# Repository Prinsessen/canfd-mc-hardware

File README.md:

# CANFD-MC — a minimal CAN board for a motorcycle

A 55 × 32 mm, 4-layer board that replaces the LilyGO T-2CANFD in the
[indian-thunderstroke-canbus](https://github.com/Prinsessen/indian-thunderstroke-canbus)
project: ESP32-S3-WROOM-1U + MCP2518FD + TCAN332G, fed from the bike's
permanent 12 V through an LM5164 buck. Same pin map as the LilyGO board, so the
firmware runs unchanged (`sniffer-t2can` environment).

What it drops from the LilyGO board, on purpose: the isolated transceiver (one
machine, one ground — the isolation was bridged the moment it was wired in, and
its DC-DC was three quarters of the sleep current), the USB connector, the screw
terminals, the second CAN channel, and the 120 Ω termination (the bike's bus is
already terminated; a third resistor is a stub). What it adds: a 6–40 V input
that survives load dump, four solder pads with strain-relief holes instead of
connectors, and a ~10 µA regulator so the board can live on the battery.

## Layout

```
canfd-mc.kicad_pro / .kicad_sch / .kicad_pcb   KiCad 10 project — placed, routed, DRC clean
canfd_local.pretty/                            three project footprints (solder pads with relief
                                               holes, Murata DLW43SH with Murata's pin numbering)
production/                                    what JLCPCB was sent: Gerber zip, BOM, CPL
docs/design-document.html                      the full design document: BOM, net list, the
                                               LM5164 calculation, layout rules, checklist
docs/BUILD-NOTES.md                            build, ordering and bring-up notes
docs/WIRING-PARTS.md                           antenna and service-connector cable to order
```

## Connections

Four wires from the service connector, soldered to plated pads along the bottom
edge — **CANL · CANH · GND · VBAT**. Each pad has an unplated 1.2 mm hole 3 mm
inboard: thread the wire up through the hole and down into the pad, so the
board takes the strain instead of the solder joint. No shield pad: the bus
shield is grounded at the ECM.

Flash header on the back (through-hole from rev 1.1, flat pads on rev 1.0), 2.54 mm pitch —
**GND · EN · TX · RX · IO0 · USB_D+ · USB_D−**.
First flash goes over the ESP32-S3's native USB (a cut USB cable on D+/D−/GND;
the board is powered from 12 V, not from USB). After that, OTA.

## Power input

| | |
|---|---|
| Input | 6–40 V (LM5164 is rated to 100 V; the TVS clamps load dump at ~39 V) |
| UVLO | on at 7.0 V, off at 6.5 V |
| Output | 3.3 V, 300 kHz, 1 A rating (real load < 0.5 A) |
| Protection | 1 A fuse, series Schottky (reverse polarity), SMBJ24CA |

The buck was calculated from the LM5164 datasheet equations and confirmed with
TI's WEBENCH: RON, inductor and bootstrap capacitor came out identical.

## Status

Rev 1.0 ordered from JLCPCB in September 2026 (5 boards, assembled) — on `main`.
Rev 1.1 (85 °C module, through-hole flash header and test pads) is on the
`rev1.1` branch, ready but unordered until rev 1.0 has been tested. Reviewed
([docs/REVIEW-rev1.0.md](docs/REVIEW-rev1.0.md)): net list confirmed against the
datasheets, three notes for rev 1.1. Not yet tested on
hardware — this is a first revision, and the bring-up checklist in the design
document is the plan for finding out what it got wrong.

Things a second revision might change are tracked in the design document's
open-points table.

## Licence

MIT, like the firmware. Design and silkscreen: Springcommand — Nanna Agesen 2026.

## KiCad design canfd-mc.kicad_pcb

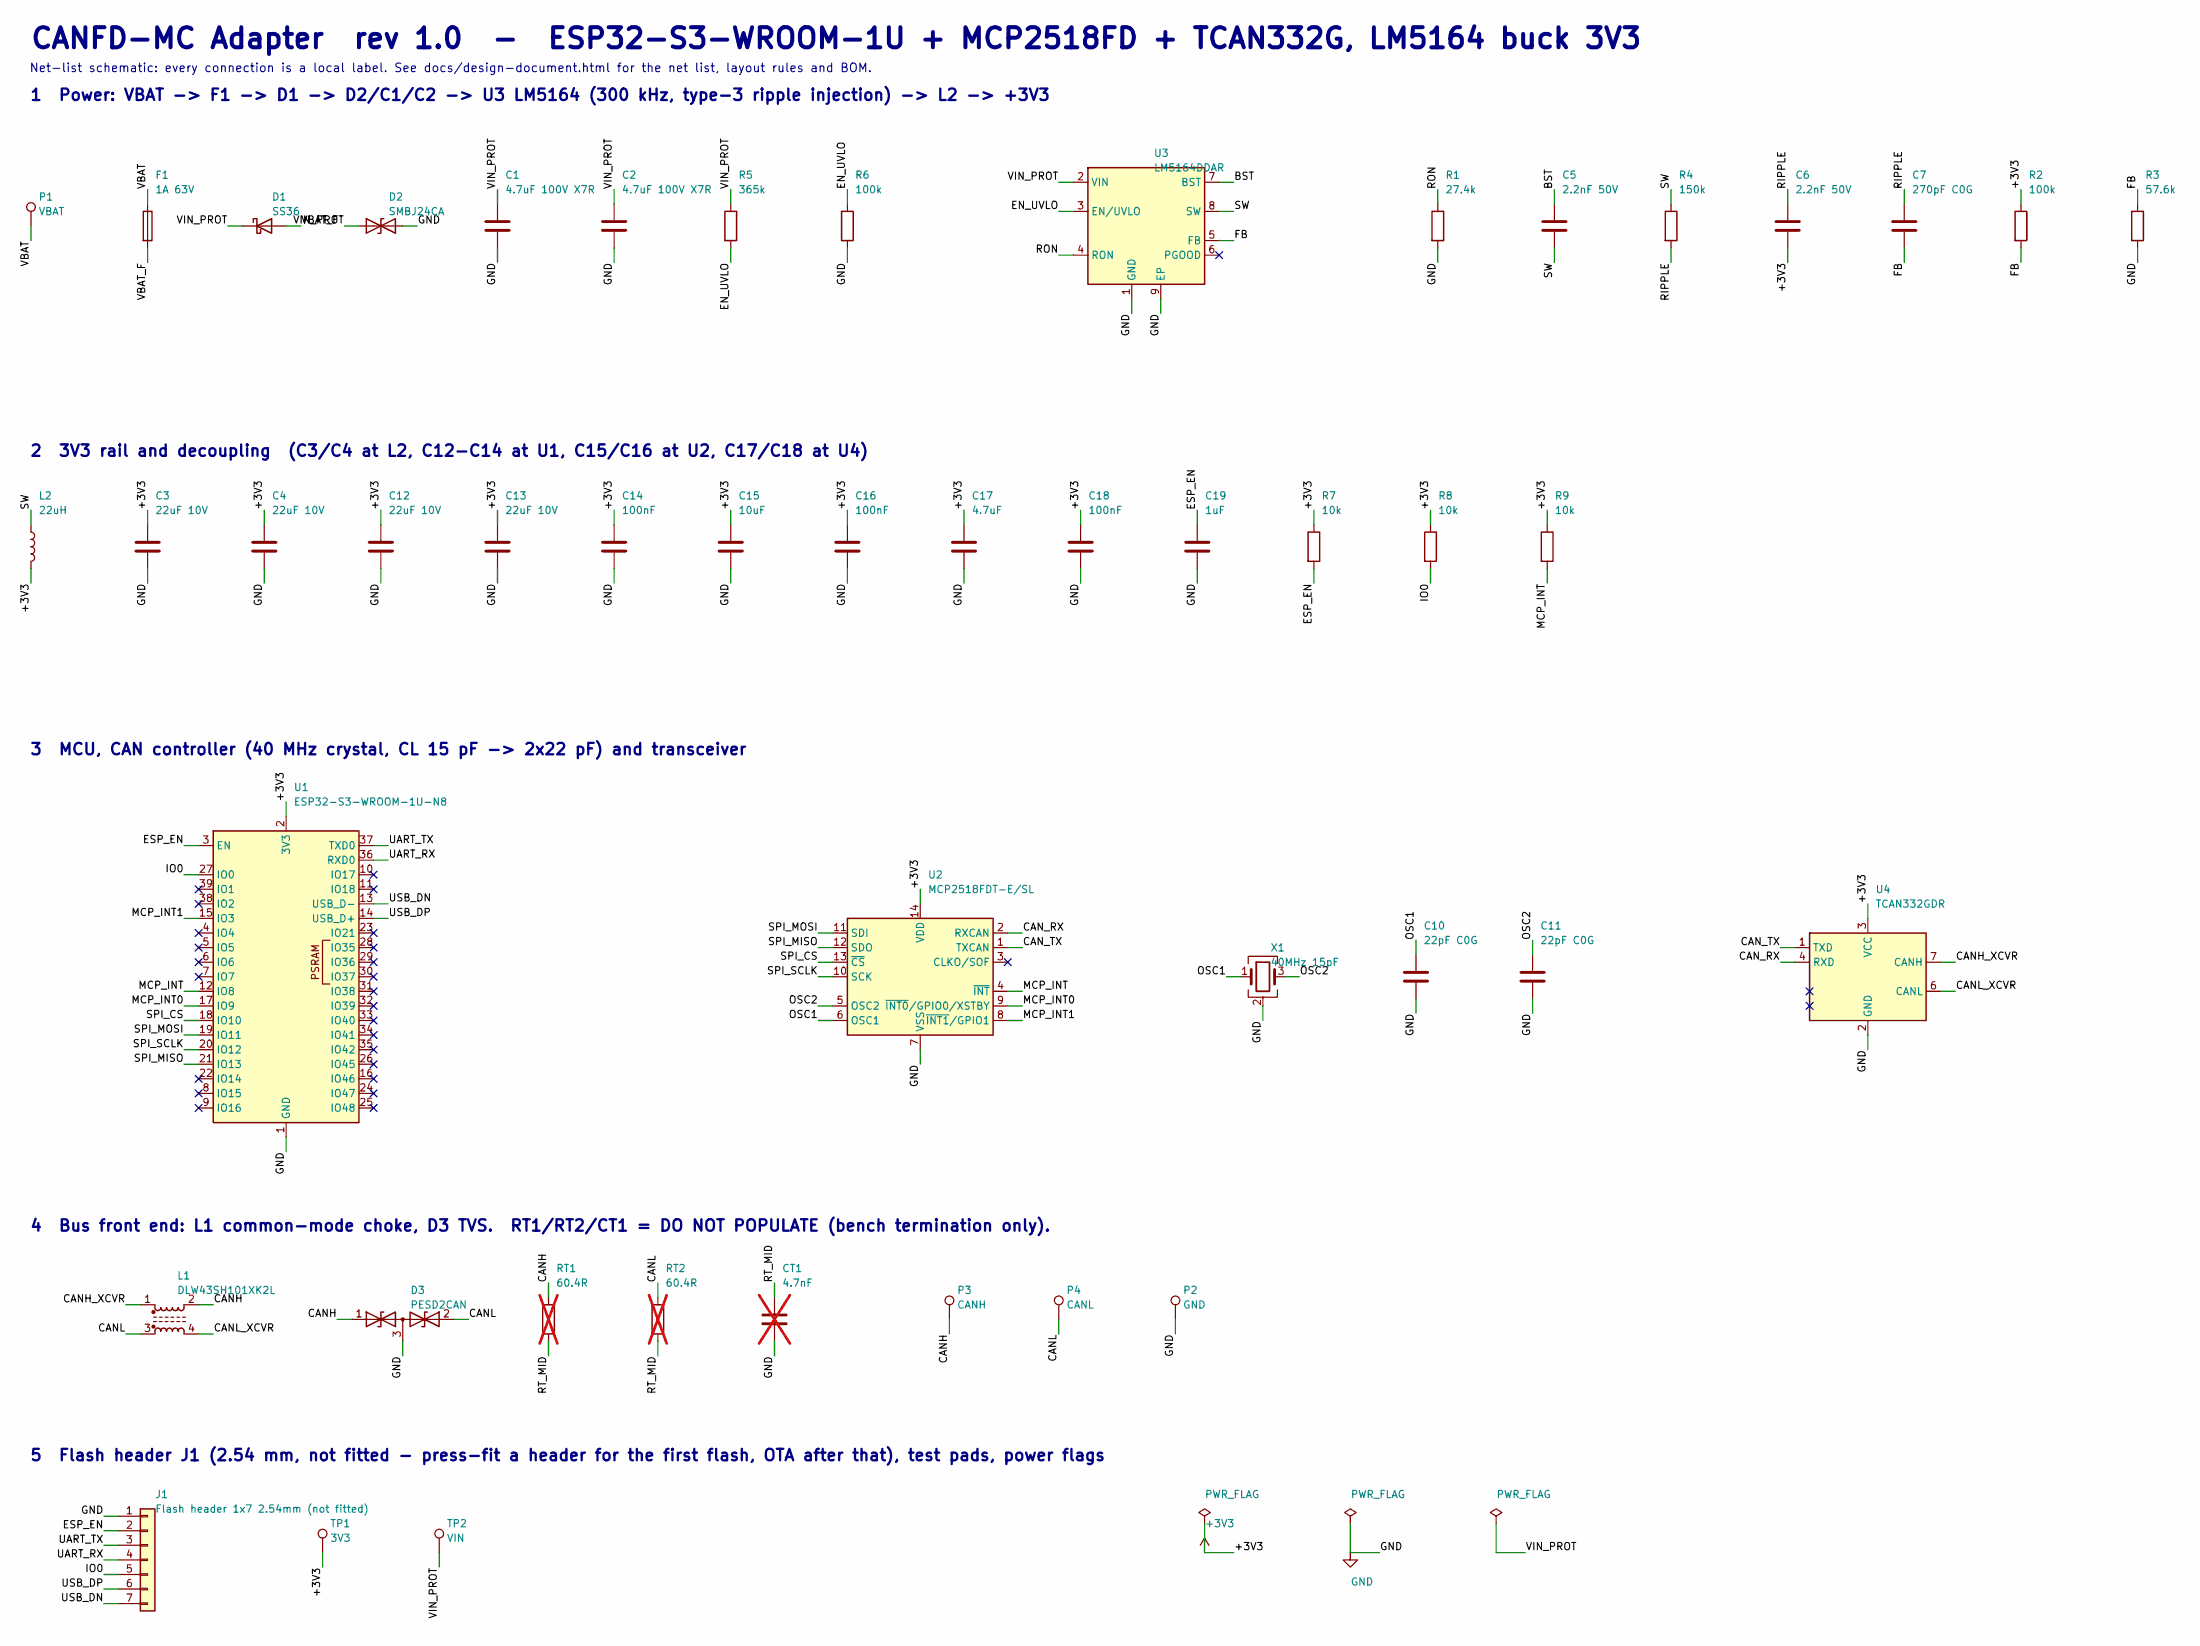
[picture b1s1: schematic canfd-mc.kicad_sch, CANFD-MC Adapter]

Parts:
C1, C2: 4.7uF 100V X7R; C_1210_3225Metric; LCSC C385986
C3, C4, C12, C13: 22uF 10V; C_0805_2012Metric; LCSC C45783
C5, C6: 2.2nF 50V; C_0603_1608Metric; LCSC C1604
C7: 270pF C0G; C_0603_1608Metric; LCSC C1657
C10, C11: 22pF C0G; C_0603_1608Metric; LCSC C1653
C14, C16, C18: 100nF; C_0603_1608Metric; LCSC C14663
C15: 10uF; C_0603_1608Metric; LCSC C19702
C17: 4.7uF; C_0603_1608Metric; LCSC C19666
C19: 1uF; C_0603_1608Metric; LCSC C15849
CT1: 4.7nF; C_0603_1608Metric; LCSC C53987; not fitted
D1: SS36; D_SMA; LCSC C16015
D2: SMBJ24CA; D_SMB; LCSC C83268
D3: PESD2CAN; SOT-23; LCSC C75176
F1: 1A 63V; Fuse_1206_3216Metric; LCSC C151135
J1: Flash header 1x7 2.54mm (not fitted); PinHeader_1x07_P2.54mm_Vertical
L1: DLW43SH101XK2L; L_CommonModeChoke_Murata_DLW43SH; LCSC C123085
L2: 22uH; L_Changjiang_FNR5040S; LCSC C167971
P1: VBAT; SolderPad_D2.0mm_Relief
P2: GND; SolderPad_D2.0mm_Relief
P3: CANH; SolderPad_D1.5mm_Relief
P4: CANL; SolderPad_D1.5mm_Relief
R1: 27.4k; R_0603_1608Metric; LCSC C22964
R2, R6: 100k; R_0603_1608Metric; LCSC C25803
R3: 57.6k; R_0603_1608Metric; LCSC C23082
R4: 150k; R_0603_1608Metric; LCSC C22807
R5: 365k; R_0603_1608Metric; LCSC C23031
R7, R8, R9: 10k; R_0603_1608Metric; LCSC C25804
RT1, RT2: 60.4R; R_1206_3216Metric; LCSC C72998; not fitted
TP1: 3V3; PinHeader_1x01_P2.54mm_Vertical
TP2: VIN; PinHeader_1x01_P2.54mm_Vertical
U1: ESP32-S3-WROOM-1U-N8; ESP32-S3-WROOM-1U; LCSC C2980297
U2: MCP2518FDT-E/SL; SOIC-14_3.9x8.7mm_P1.27mm; LCSC C626758
U3: LM5164DDAR; TI_SO-PowerPAD-8_ThermalVias; LCSC C477928
U4: TCAN332GDR; SOIC-8_3.9x4.9mm_P1.27mm; LCSC C191010
X1: 40MHz 15pF; Crystal_SMD_3225-4Pin_3.2x2.5mm; LCSC C9010

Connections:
+3V3: C3.1, C4.1, C6.2, C12.1, C13.1, C14.1, C15.1, C16.1, C17.1, C18.1, L2.2, R2.1, R7.1, R8.1, R9.1, TP1.1, U1.2 (3V3), U2.14 (VDD), U4.3 (VCC)
/BST: C5.1, U3.7 (BST)
/CANH: D3.1 (A1), L1.2, P3.1 (1_1), RT1.1
/CANH_XCVR: L1.1, U4.7 (CANH)
/CANL: D3.2 (A2), L1.3, P4.1 (1_1), RT2.1
/CANL_XCVR: L1.4, U4.6 (CANL)
/CAN_RX: U2.2 (RXCAN), U4.4 (RXD)
/CAN_TX: U2.1 (TXCAN), U4.1 (TXD)
/EN_UVLO: R5.2, R6.1, U3.3 (EN/UVLO)
/ESP_EN: C19.1, J1.2, R7.2, U1.3 (EN)
/FB: C7.2, R2.2, R3.1, U3.5 (FB)
/IO0: J1.5, R8.2, U1.27 (IO0)
/MCP_INT: R9.2, U1.12 (IO8), U2.4 (~INT)
/MCP_INT0: U1.17 (IO9), U2.9 (~INT0/GPIO0/XSTBY)
/MCP_INT1: U1.15 (IO3), U2.8 (~INT1/GPIO1)
/OSC1: C10.1, U2.6 (OSC1), X1.1
/OSC2: C11.1, U2.5 (OSC2), X1.3
/RIPPLE: C6.1, C7.1, R4.2
/RON: R1.1, U3.4 (RON)
/RT_MID: CT1.1, RT1.2, RT2.2
/SPI_CS: U1.18 (IO10), U2.13 (~CS)
/SPI_MISO: U1.21 (IO13), U2.12 (SDO)
/SPI_MOSI: U1.19 (IO11), U2.11 (SDI)
/SPI_SCLK: U1.20 (IO12), U2.10 (SCK)
/SW: C5.2, L2.1, R4.1, U3.8 (SW)
/UART_RX: J1.4, U1.36 (RXD0)
/UART_TX: J1.3, U1.37 (TXD0)
/USB_DN: J1.7, U1.13 (USB_D-)
/USB_DP: J1.6, U1.14 (USB_D+)
/VBAT: F1.1, P1.1 (1_1)
/VBAT_F: D1.2 (A), F1.2
/VIN_PROT: C1.1, C2.1, D1.1 (K), D2.1 (A1), R5.1, TP2.1, U3.2 (VIN)
GND: C1.2, C2.2, C3.2, C4.2, C10.2, C11.2, C12.2, C13.2, C14.2, C15.2, C16.2, C17.2, C18.2, C19.2, CT1.2, D2.2 (A2), D3.3 (common), J1.1, P2.1 (1_1), R1.2, R3.2, R6.2, U1.1 (GND), U1.40 (GND), U1.41 (GND), U2.7 (VSS), U3.1 (GND), U3.9 (EP), U4.2 (GND), X1.2 (G), X1.4 (G)

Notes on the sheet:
CANFD-MC Adapter rev 1.0 - ESP32-S3-WROOM-1U + MCP2518FD + TCAN332G, LM5164 buck 3V3
Net-list schematic: every connection is a local label. See docs/design-document.html for the net list, layout rules and BOM.
1 Power: VBAT -> F1 -> D1 -> D2/C1/C2 -> U3 LM5164 (300 kHz, type-3 ripple injection) -> L2 -> +3V3
2 3V3 rail and decoupling (C3/C4 at L2, C12-C14 at U1, C15/C16 at U2, C17/C18 at U4)
3 MCU, CAN controller (40 MHz crystal, CL 15 pF -> 2x22 pF) and transceiver
4 Bus front end: L1 common-mode choke, D3 TVS. RT1/RT2/CT1 = DO NOT POPULATE (bench termination only).
5 Flash header J1 (2.54 mm, not fitted - press-fit a header for the first flash, OTA after that), test pads, power flags

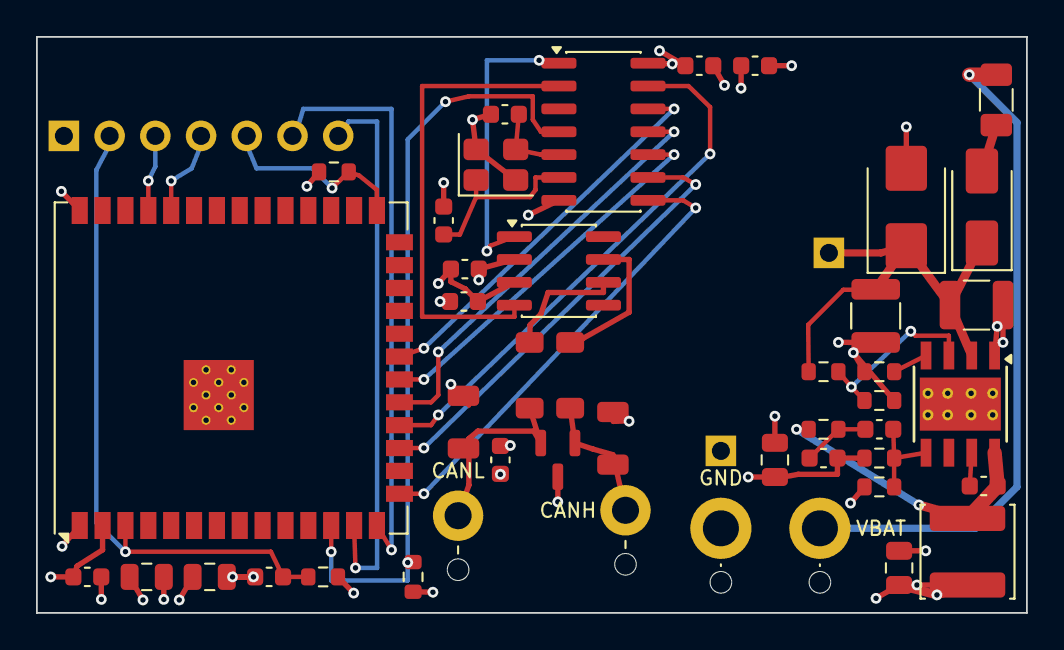
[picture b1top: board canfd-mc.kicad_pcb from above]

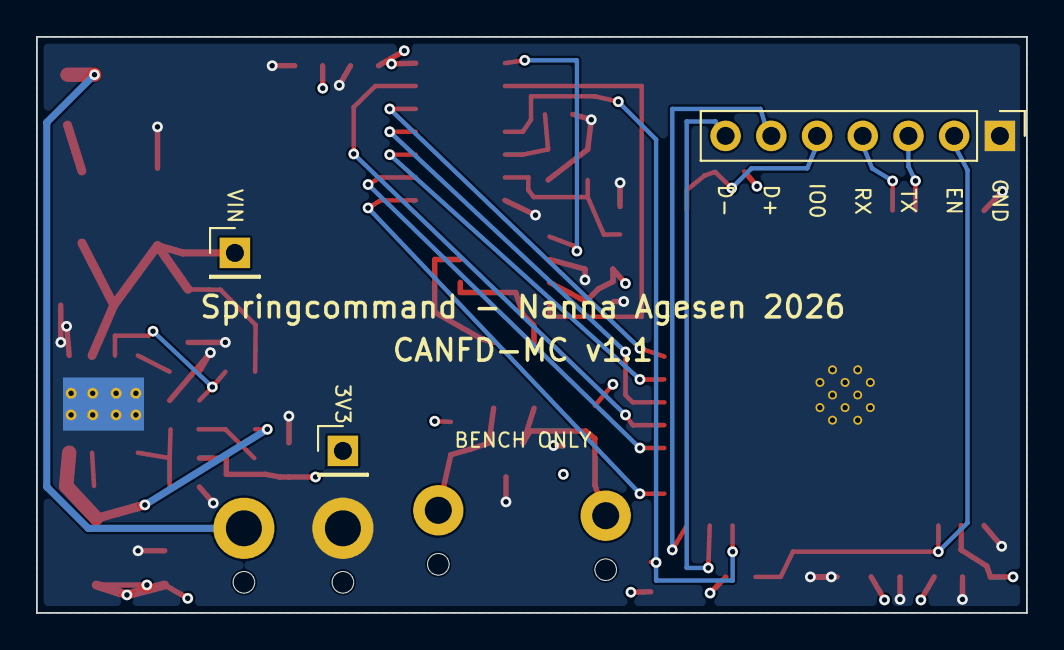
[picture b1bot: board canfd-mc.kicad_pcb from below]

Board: 4 copper layers, 55.0 x 32.0 mm, 47 parts (3 on the bottom side), 33 nets.

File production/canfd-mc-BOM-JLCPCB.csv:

Comment,Designator,Footprint,LCSC Part #
4.7uF 100V X7R,"C1,C2",C_1210_3225Metric,C385986
22uF 10V,"C3,C4,C12,C13",C_0805_2012Metric,C45783
2.2nF 50V,"C5,C6",C_0603_1608Metric,C1604
270pF C0G,C7,C_0603_1608Metric,C1657
22pF C0G,"C10,C11",C_0603_1608Metric,C1653
100nF,"C14,C16,C18",C_0603_1608Metric,C14663
10uF,C15,C_0603_1608Metric,C19702
4.7uF,C17,C_0603_1608Metric,C19666
1uF,C19,C_0603_1608Metric,C15849
SS36,D1,D_SMA,C16015
SMBJ24CA,D2,D_SMB,C83268
PESD2CAN,D3,SOT-23,C75176
1A 63V,F1,Fuse_1206_3216Metric,C151135
DLW43SH101XK2L,L1,L_CommonModeChoke_Murata_DLW43SH,C123085
22uH,L2,L_Changjiang_FNR5040S,C167971
27.4k,R1,R_0603_1608Metric,C22964
100k,"R2,R6",R_0603_1608Metric,C25803
57.6k,R3,R_0603_1608Metric,C23082
150k,R4,R_0603_1608Metric,C22807
365k,R5,R_0603_1608Metric,C23031
10k,"R7,R8,R9",R_0603_1608Metric,C25804
ESP32-S3-WROOM-1U-N8,U1,ESP32-S3-WROOM-1U,C2980297
MCP2518FDT-E/SL,U2,SOIC-14_3.9x8.7mm_P1.27mm,C626758
LM5164DDAR,U3,TI_SO-PowerPAD-8_ThermalVias,C477928
TCAN332GDR,U4,SOIC-8_3.9x4.9mm_P1.27mm,C191010
40MHz 15pF,X1,Crystal_SMD_3225-4Pin_3.2x2.5mm,C9010
